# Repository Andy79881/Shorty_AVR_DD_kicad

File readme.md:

# Shorty_AVR_DD - Kicad based design files

## What is it for?

Shorty is short circuit finder, usable for checking PCB, for example. Where normal digital multimeters do not have enough of resolution to differentiate low PCB resistance in order of tens of miliohms to allow exact short circuit location, shorty comes to help.

## Content of this repository

This repository consists of the Kicad files. The design is done with Kicad 9.x.

Code Baseline:
---
- Refer to Readme of [Shorty_AVR_DD](https://github.com/Andy79881/Shorty_AVR_DD).

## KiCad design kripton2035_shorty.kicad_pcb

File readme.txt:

Export Gerber and Drill files
-------------------------------

Aisler: https://community.aisler.net/t/support-for-traditional-gerber-files/99

1.) Dateinamen des Export können so bleiben!

Lesson Learned
---------------

Aisler HASL Design-Regeln verletzt -> ENIG musste genutzt werden (teurer aber auch höherwertiger)
-> min via annular ring 200um -> aktuell Design rules 300um Bohrung und 600um Via = 150um annular ring
-> für HASL müsste DK Durchmesser 700um bei 300um Bohrdurchmesser betragen

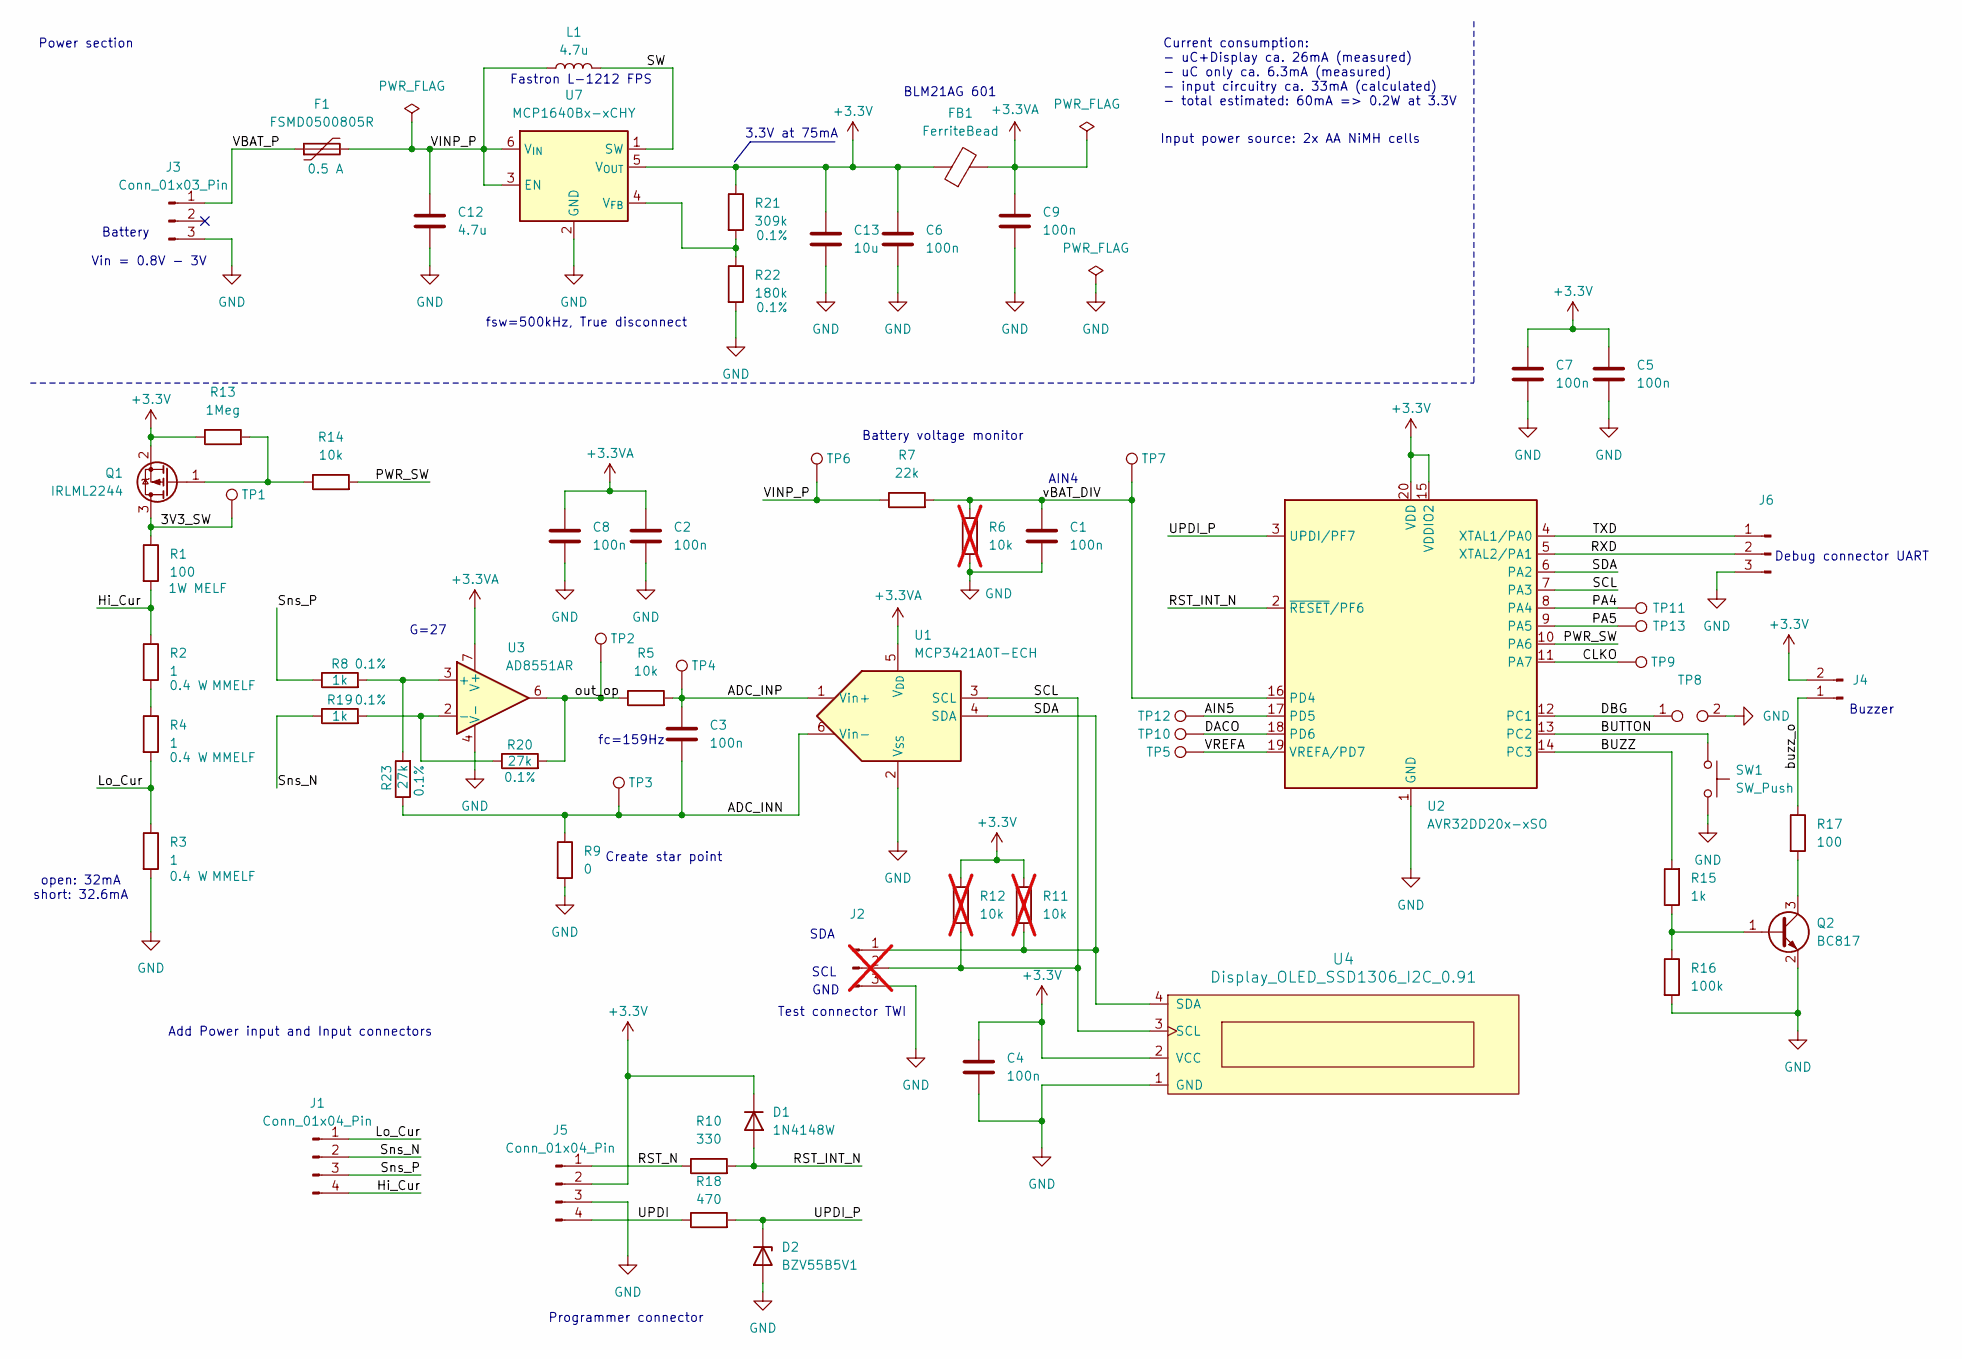
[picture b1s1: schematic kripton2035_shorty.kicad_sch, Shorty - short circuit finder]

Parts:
C1, C2, C3, C4, C5, C6, C7, C8, C9: 100n; C_0805_2012Metric_Pad1.18x1.45mm_HandSolder
C12: 4.7u; C_0805_2012Metric_Pad1.18x1.45mm_HandSolder
C13: 10u; C_0805_2012Metric_Pad1.18x1.45mm_HandSolder
D1: 1N4148W; D_SOD-123
D2: BZV55B5V1; D_MiniMELF
F1: FSMD0500805R; Fuse_0805_2012Metric_Pad1.15x1.40mm_HandSolder; Voltage 6 V
FB1: FerriteBead; L_0805_2012Metric_Pad1.15x1.40mm_HandSolder
J1: Conn_01x04_Pin; JST_XH_S4B-XH-A_1x04_P2.50mm_Horizontal
J2: Conn_01x03_Pin; PinHeader_1x03_P2.54mm_Vertical; not fitted
J3: Conn_01x03_Pin; JST_PH_B3B-PH-K_1x03_P2.00mm_Vertical
J4: Conn_01x02_Pin; JST_PH_B2B-PH-K_1x02_P2.00mm_Vertical
J5: Conn_01x04_Pin; PinHeader_1x04_P2.54mm_Vertical
J6: Conn_01x03_Pin; PinHeader_1x03_P2.54mm_Vertical
L1: 4.7u; L_Fastron-1212FPS
Q1: IRLML2244; SOT-23
Q2: BC817; SOT-23
R1: 100; R_MELF_MMB-0207
R2, R3, R4: 1; R_MiniMELF_MMA-0204
R5, R14: 10k; R_0805_2012Metric_Pad1.20x1.40mm_HandSolder
R6: 10k; R_0805_2012Metric_Pad1.20x1.40mm_HandSolder; not fitted
R7: 22k; R_0805_2012Metric_Pad1.20x1.40mm_HandSolder
R8, R15, R19: 1k; R_0805_2012Metric_Pad1.20x1.40mm_HandSolder
R9: 0; R_0805_2012Metric_Pad1.20x1.40mm_HandSolder
R10: 330; R_0805_2012Metric_Pad1.20x1.40mm_HandSolder
R11, R12: 10k; R_1206_3216Metric_Pad1.30x1.75mm_HandSolder; not fitted
R13: 1Meg; R_0805_2012Metric_Pad1.20x1.40mm_HandSolder
R16: 100k; R_0805_2012Metric_Pad1.20x1.40mm_HandSolder
R17: 100; R_0805_2012Metric_Pad1.20x1.40mm_HandSolder
R18: 470; R_0805_2012Metric_Pad1.20x1.40mm_HandSolder
R20, R23: 27k; R_0805_2012Metric_Pad1.20x1.40mm_HandSolder
R21: 309k; R_0603_1608Metric_Pad0.98x0.95mm_HandSolder
R22: 180k; R_0603_1608Metric_Pad0.98x0.95mm_HandSolder
SW1: SW_Push; SW_SPST_Omron_B3F-40xx
TP1, TP2, TP3, TP4, TP5, TP6, TP7, TP9, TP10, TP11, TP12, TP13: TestPoint; TestPoint_Pad_D1.0mm
TP8: TestPoint_2Pole; TestPoint_2Pads_Pitch2.54mm_Drill0.8mm
U1: MCP3421A0T-ECH; SOT-23-6
U2: AVR32DD20x-xSO; SOIC-20W_7.5x12.8mm_P1.27mm
U3: AD8551AR; SOIC-8_3.9x4.9mm_P1.27mm
U4: Display_OLED_SSD1306_I2C_0.91; SSD1306-0.91-OLED-4pin-128x32
U7: MCP1640Bx-xCHY; SOT-23-6

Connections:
+3.3V: C4.1, C5.1, C6.1, C7.1, C13.1, D1.1 (K), FB1.1, J4.2, J5.2, Q1.2 (S), R11.2, R12.2, R13.1, R21.1, U2.15 (VDDIO2), U2.20 (VDD), U4.2 (VCC), U7.5 (V_{OUT})
+3.3VA: C2.1, C8.1, C9.1, FB1.2, U1.5 (V_{DD}), U3.7 (V+)
/3V3_SW: Q1.3 (D), R1.1, TP1.1
/ADC_INN: C3.2, R9.1, R23.1, TP3.1, U1.6 (Vin-)
/ADC_INP: C3.1, R5.2, TP4.1, U1.1 (Vin+)
/AIN5: TP12.1, U2.17 (PD5)
/BUTTON: SW1.1, U2.13 (PC2)
/BUZZ: R15.2, U2.14 (PC3)
/CLKO: TP9.1, U2.11 (PA7)
/DACO: TP10.1, U2.18 (PD6)
/DBG: TP8.1, U2.12 (PC1)
/Hi_Cur: J1.4, R1.2, R2.1
/Lo_Cur: J1.1, R3.1, R4.2
/PA4: TP11.1, U2.8 (PA4)
/PA5: TP13.1, U2.9 (PA5)
/PWR_SW: R14.2, U2.10 (PA6)
/RST_INT_N: D1.2 (A), R10.2, U2.2 (~RESET/PF6)
/RST_N: J5.1, R10.1
/RXD: J6.2, U2.5 (XTAL2/PA1)
/SCL: J2.2, R12.1, U1.3 (SCL), U2.7 (PA3), U4.3 (SCL)
/SDA: J2.1, R11.1, U1.4 (SDA), U2.6 (PA2), U4.4 (SDA)
/SW: L1.2, U7.1 (SW)
/Sns_N: J1.2, R19.1
/Sns_P: J1.3, R8.1
/TXD: J6.1, U2.4 (XTAL1/PA0)
/UPDI: J5.4, R18.1
/UPDI_P: D2.1 (K), R18.2, U2.3 (UPDI/PF7)
/VBAT_P: F1.1, J3.1
/VINP_P: C12.1, F1.2, L1.1, R7.1, TP6.1, U7.3 (EN), U7.6 (V_{IN})
/VREFA: TP5.1, U2.19 (VREFA/PD7)
/buzz_o: J4.1, R17.1
/out_op: R5.1, R20.2, TP2.1, U3.6
/vBAT_DIV: C1.1, R6.1, R7.2, TP7.1, U2.16 (PD4)
GND: C1.2, C2.2, C4.2, C5.2, C6.2, C7.2, C8.2, C9.2, C12.2, C13.2, D2.2 (A), J2.3, J3.3, J5.3, J6.3, Q2.2 (E), R3.2, R6.2, R9.2, R16.2, R22.2, SW1.2, TP8.2, U1.2 (V_{SS}), U2.1 (GND), U3.4 (V-), U4.1 (GND), U7.2 (GND)
unnamed: Q1.1 (G), R13.2, R14.1
unnamed: Q2.1 (B), R15.1, R16.1
unnamed: Q2.3 (C), R17.2
unnamed: R2.2, R4.1
unnamed: R8.2, R23.2, U3.3 (+)
unnamed: R19.2, R20.1, U3.2 (-)
unnamed: R21.2, R22.1, U7.4 (V_{FB})

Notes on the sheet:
Test connector TWI
Buzzer
Current consumption: - uC+Display ca. 26mA (measured) - uC only ca. 6.3mA (measured) - input circuitry ca. 33mA (calculated) - total estimated: 60mA => 0.2W at 3.3V
fc=159Hz
Vin = 0.8V - 3V
Add Power input and Input connectors
3.3V at 75mA
Fastron L-1212 FPS
AIN4
Power section
open: 32mA short: 32.6mA
SCL
Battery voltage monitor
Battery
Input power source: 2x AA NiMH cells
G=27
Debug connector UART
GND
SDA
Create star point
Programmer connector
fsw=500kHz, True disconnect
BLM21AG 601

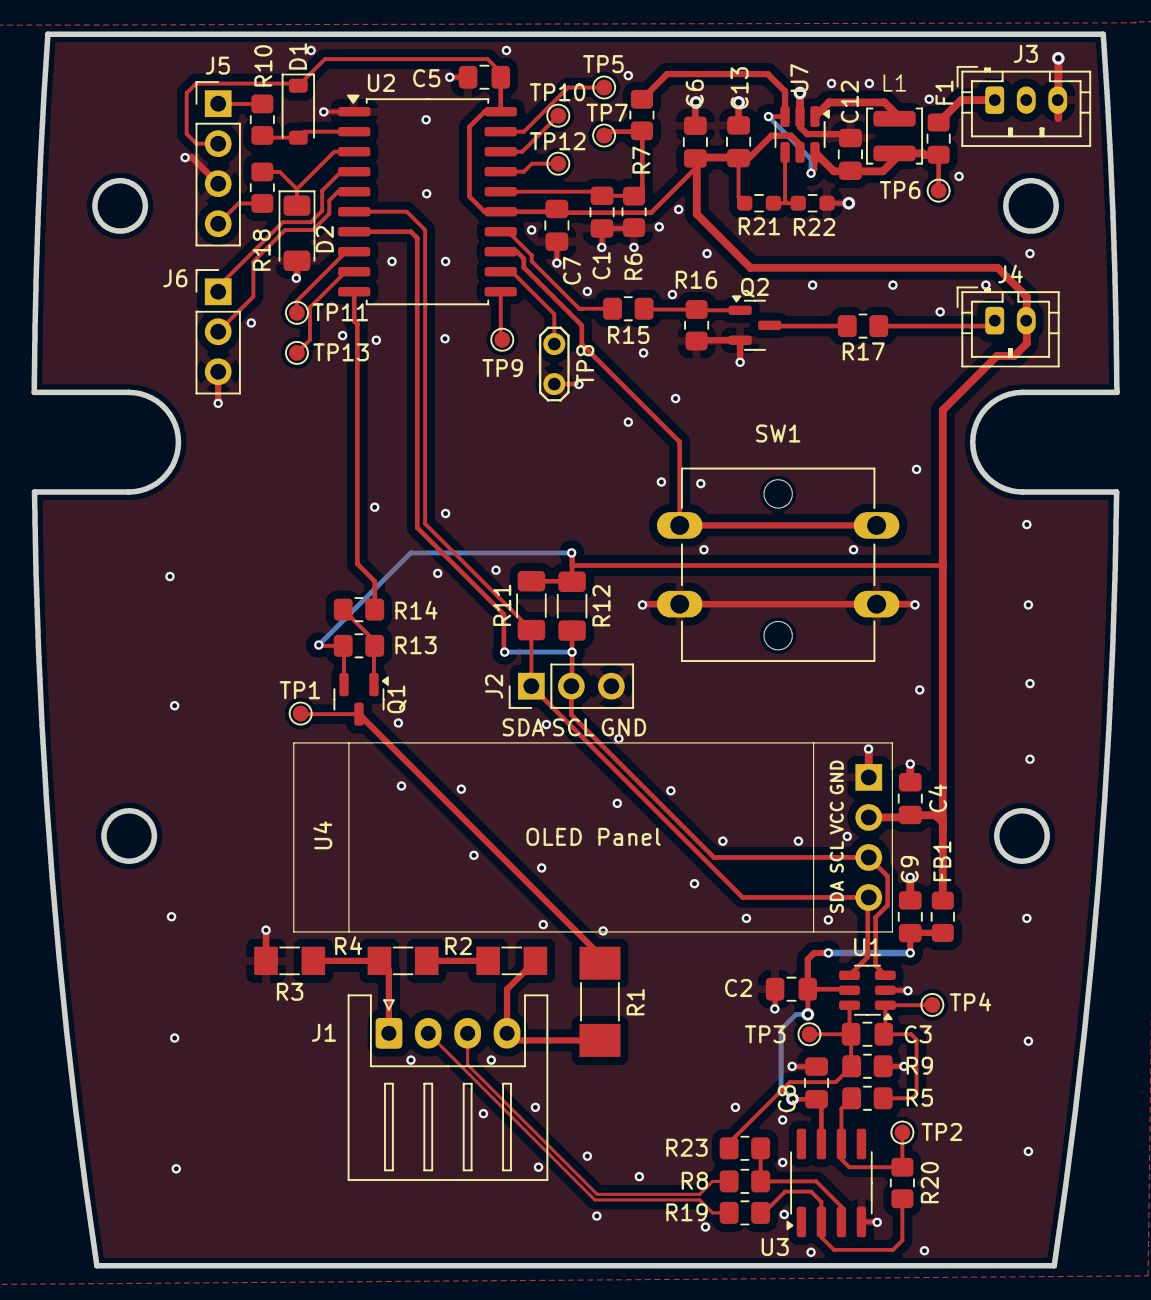
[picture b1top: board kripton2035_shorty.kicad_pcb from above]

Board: 2 copper layers, 68.7 x 78.2 mm, 66 parts (0 on the bottom side), 41 nets.

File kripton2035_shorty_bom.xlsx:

Reference | Value | Datasheet | Footprint | Qty | DNP
C1,C2,C3,C4,C5,C6,C7,C8,C9 | 100n | ~ | Capacitor_SMD:C_0805_2012Metric_Pad1.18x1.45mm_HandSolder | 9
C12,L1 | 4.7u | https://www.fastrongroup.com/uploads/datasheets/Series/Compl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 | Capacitor_SMD:C_1210_3225Metric_Pad1.33x2.70mm_HandSolder,user_global_passive_l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 | 2
C13 | 10u | ~ | Capacitor_SMD:C_1210_3225Metric_Pad1.33x2.70mm_HandSolder | 1
D1 | 1N4148W | https://www.vishay.com/docs/85748/1n4148w.pdf | Diode_SMD:D_SOD-123 | 1
D2 | BZV55B5V1 | https://assets.nexperia.com/documents/data-sheet/BZV55_SER.pdf | Diode_SMD:D_MiniMELF | 1
F1 | FSMD0500805R | ~ | Fuse:Fuse_0805_2012Metric_Pad1.15x1.40mm_HandSolder | 1
FB1 | FerriteBead | ~ | Inductor_SMD:L_0805_2012Metric_Pad1.15x1.40mm_HandSolder | 1
J1,J5 | Conn_01x04_Pin | ~ | Connector_JST:JST_XH_S4B-XH-A_1x04_P2.50mm_Horizontal,Connector_PinHeader_2.54m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 | 2
J2 | Conn_01x03_Pin | ~ | Connector_PinHeader_2.54mm:PinHeader_1x03_P2.54mm_Vertical | 1 | DNP
J3,J6 | Conn_01x03_Pin | ~ | Connector_JST:JST_PH_B3B-PH-K_1x03_P2.00mm_Vertical,Connector_PinHeader_2.54mm: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 | 2
J4 | Conn_01x02_Pin | ~ | Connector_JST:JST_PH_B2B-PH-K_1x02_P2.00mm_Vertical | 1
Q1 | IRLML2244 | https://www.infineon.com/dgdl/irlml6401pbf.pdf?fileId=5546d4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 | Package_TO_SOT_SMD:SOT-23 | 1
Q2 | BC817 | https://www.onsemi.com/pub/Collateral/BC818-D.pdf | Package_TO_SOT_SMD:SOT-23 | 1
R1,R17 | 100 | ~ | Resistor_SMD:R_0805_2012Metric_Pad1.20x1.40mm_HandSolder,Resistor_SMD:R_MELF_MM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 | 2
R2,R3,R4 | 1 | ~ | Resistor_SMD:R_MiniMELF_MMA-0204 | 3
R5,R14 | 10k | ~ | Resistor_SMD:R_0805_2012Metric_Pad1.20x1.40mm_HandSolder | 2
R6,R11,R12 | 10k | ~ | Resistor_SMD:R_0805_2012Metric_Pad1.20x1.40mm_HandSolder,Resistor_SMD:R_1206_32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 | 3 | DNP
R7 | 22k | ~ | Resistor_SMD:R_0805_2012Metric_Pad1.20x1.40mm_HandSolder | 1
R8,R15,R19 | 1k | ~ | Resistor_SMD:R_0805_2012Metric_Pad1.20x1.40mm_HandSolder | 3
R9 | 0 | ~ | Resistor_SMD:R_0805_2012Metric_Pad1.20x1.40mm_HandSolder | 1
R10 | 330 | ~ | Resistor_SMD:R_0805_2012Metric_Pad1.20x1.40mm_HandSolder | 1
R13 | 1Meg | ~ | Resistor_SMD:R_0805_2012Metric_Pad1.20x1.40mm_HandSolder | 1
R16 | 100k | ~ | Resistor_SMD:R_0805_2012Metric_Pad1.20x1.40mm_HandSolder | 1
R18 | 470 | ~ | Resistor_SMD:R_0805_2012Metric_Pad1.20x1.40mm_HandSolder | 1
R20,R23 | 27k | ~ | Resistor_SMD:R_0805_2012Metric_Pad1.20x1.40mm_HandSolder | 2
R21 | 309k | ~ | Resistor_SMD:R_0603_1608Metric_Pad0.98x0.95mm_HandSolder | 1
R22 | 180k | ~ | Resistor_SMD:R_0603_1608Metric_Pad0.98x0.95mm_HandSolder | 1
SW1 | SW_Push | ~ | user_global_con_lib:SW_SPST_Omron_B3F-40xx | 1
U1 | MCP3421A0T-ECH | http://ww1.microchip.com/downloads/en/DeviceDoc/22003e.pdf | Package_TO_SOT_SMD:SOT-23-6 | 1
U2 | AVR32DD20x-xSO | https://www.microchip.com/en-us/product/AVR32DD20 | Package_SO:SOIC-20W_7.5x12.8mm_P1.27mm | 1
U3 | AD8551AR | https://www.analog.com/media/en/technical-documentation/data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 | Package_SO:SOIC-8_3.9x4.9mm_P1.27mm | 1
U4 | Display_OLED_SSD1306_I2C_0.91 | ~ | Custom_Displays:SSD1306-0.91-OLED-4pin-128x32 | 1
U7 | MCP1640Bx-xCHY | http://ww1.microchip.com/downloads/en/DeviceDoc/20002234D.pdf | Package_TO_SOT_SMD:SOT-23-6 | 1
